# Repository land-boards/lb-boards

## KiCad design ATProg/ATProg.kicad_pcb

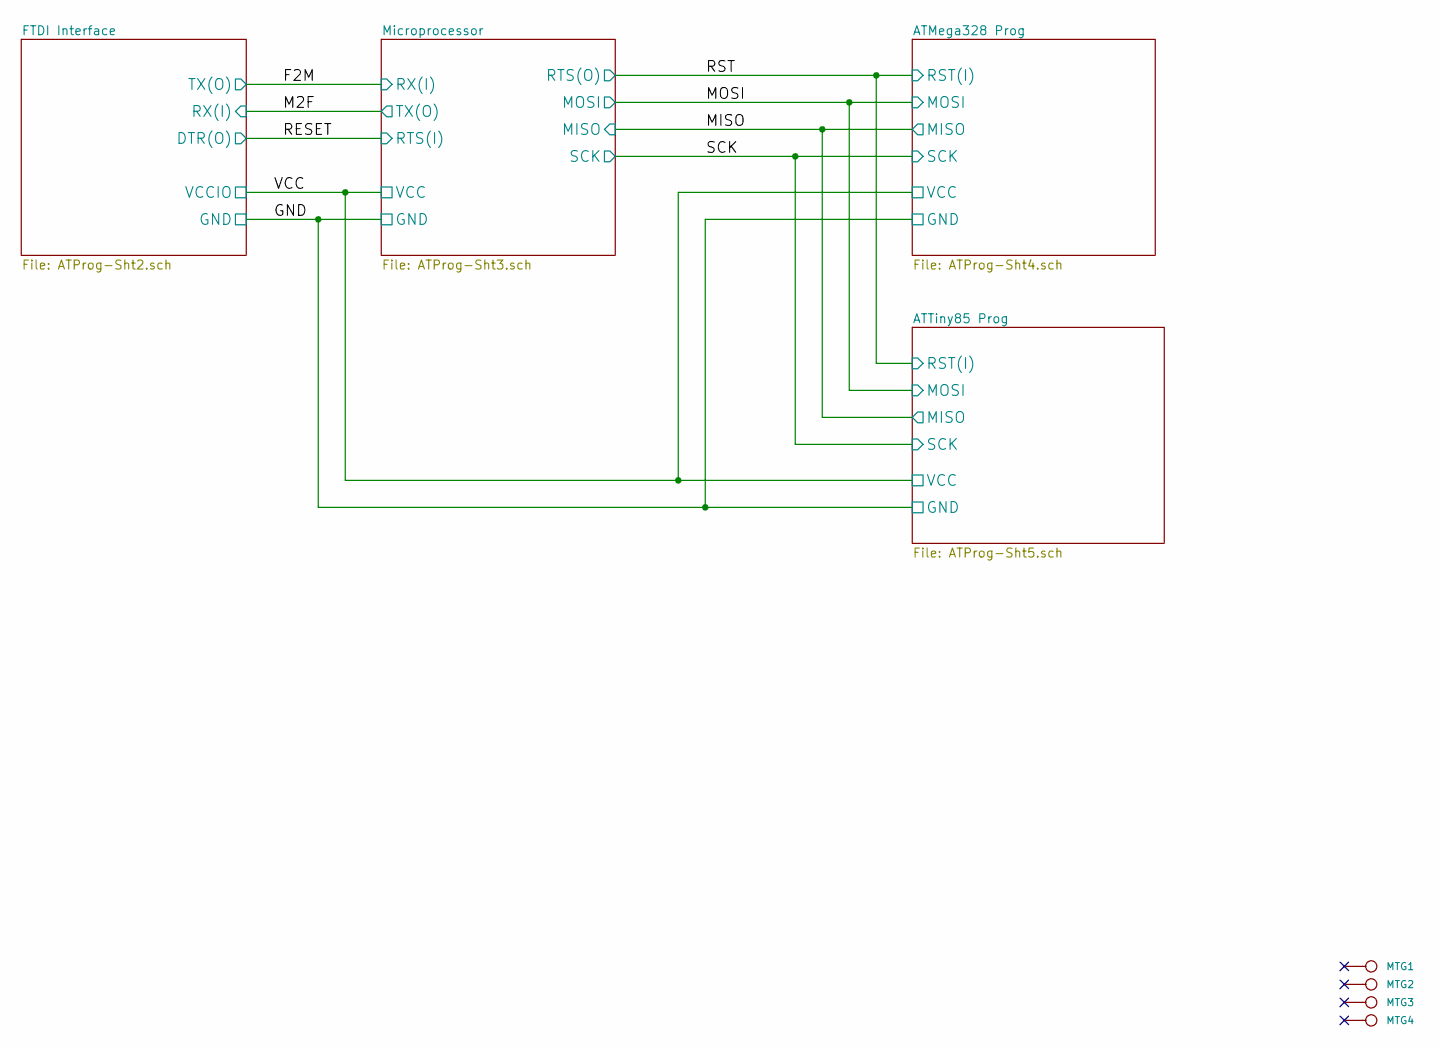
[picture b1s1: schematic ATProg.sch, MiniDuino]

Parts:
MTG1, MTG2, MTG3, MTG4: CONN_1; MTG-4-40

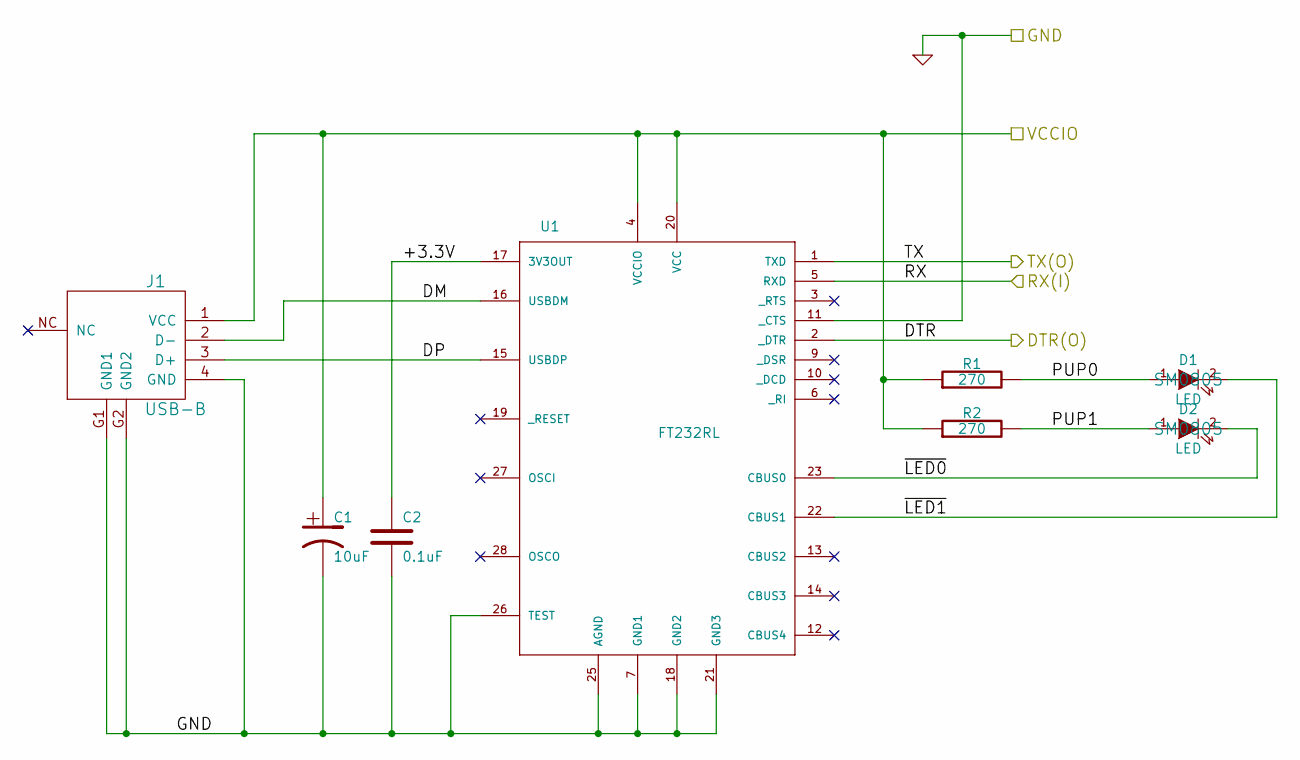
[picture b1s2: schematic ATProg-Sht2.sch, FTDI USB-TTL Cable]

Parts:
C1: 10uF; SM1210; MfgPN CC121ZKY5V8BB106
C2: 0.1uF; SM0805; MfgPN GRM155F51E104ZA1J
D1, D2: LED; SM0805
J1: USB-B; USB-B-MINI; MfgPN UX60SC-MB-5ST(80)
R1: 270; SM0805; MfgPN CRG0805F270R
R2: 270; SM0805
U1: FT232RL; SSOP28; MfgPN FT232RL-REEL

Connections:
+5V: C1.1, J1.1 (VCC), R1.1, R2.1, U1.4 (VCCIO), U1.20 (VCC); also elsewhere on the board
/FTDI Interface/+3.3V: C2.1, U1.17 (3V3OUT)
/FTDI Interface/DM: J1.2 (D-), U1.16 (USBDM)
/FTDI Interface/DP: J1.3 (D+), U1.15 (USBDP)
/FTDI Interface/DTR(O): U1.2 (_DTR); also elsewhere on the board
/FTDI Interface/PUP0: D1.1 (A), R1.2
/FTDI Interface/PUP1: D2.1 (A), R2.2
/FTDI Interface/RXFTDI: U1.5 (RXD); also elsewhere on the board
/FTDI Interface/~LED0: D2.2 (K), U1.23 (CBUS0)
/FTDI Interface/~LED1: D1.2 (K), U1.22 (CBUS1)
/Microprocessor/RXCPU: U1.1 (TXD); also elsewhere on the board
GND: C1.2, C2.2, J1.4 (GND), J1.G1 (GND1), J1.G2 (GND2), U1.7 (GND1), U1.11 (_CTS), U1.18 (GND2), U1.21 (GND3), U1.25 (AGND), U1.26 (TEST); also elsewhere on the board

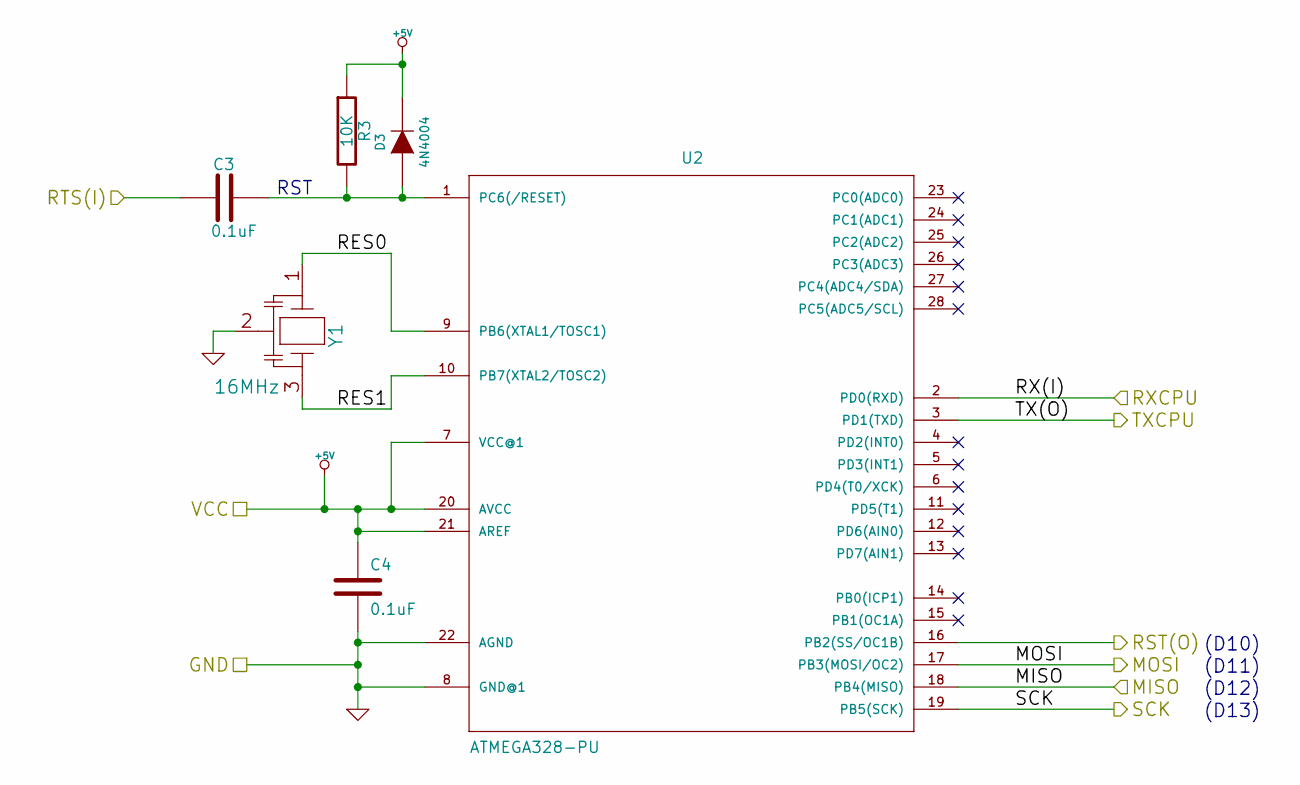
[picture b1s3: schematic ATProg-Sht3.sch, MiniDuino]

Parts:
C3, C4: 0.1uF; SM0805
D3: 4N4004; D3
R3: 10K; SM0805
U2: ATMEGA328-PU; DIP-28__300
Y1: 16MHz; SIL-3

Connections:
+5V: C4.1, D3.2 (K), R3.1, U2.7 (VCC@1), U2.20 (AVCC), U2.21 (AREF); also elsewhere on the board
/ATMega328 Prog/MISO: U2.18 (PB4(MISO)); also elsewhere on the board
/ATMega328 Prog/MOSI: U2.17 (PB3(MOSI/OC2)); also elsewhere on the board
/ATMega328 Prog/SCK: U2.19 (PB5(SCK)); also elsewhere on the board
/FTDI Interface/DTR(O): C3.1; also elsewhere on the board
/FTDI Interface/RXFTDI: U2.3 (PD1(TXD)); also elsewhere on the board
/ISP Connector/RST: U2.16 (PB2(SS/OC1B)); also elsewhere on the board
/Microprocessor/RES0: U2.9 (PB6(XTAL1/TOSC1)), Y1.1
/Microprocessor/RES1: U2.10 (PB7(XTAL2/TOSC2)), Y1.3
/Microprocessor/RXCPU: U2.2 (PD0(RXD)); also elsewhere on the board
GND: C4.2, U2.8 (GND@1), U2.22 (AGND), Y1.2; also elsewhere on the board
unnamed: C3.2, D3.1 (A), R3.2, U2.1 (PC6(/RESET))

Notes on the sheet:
(D13)
(D12)
(D11)
RST
(D10)

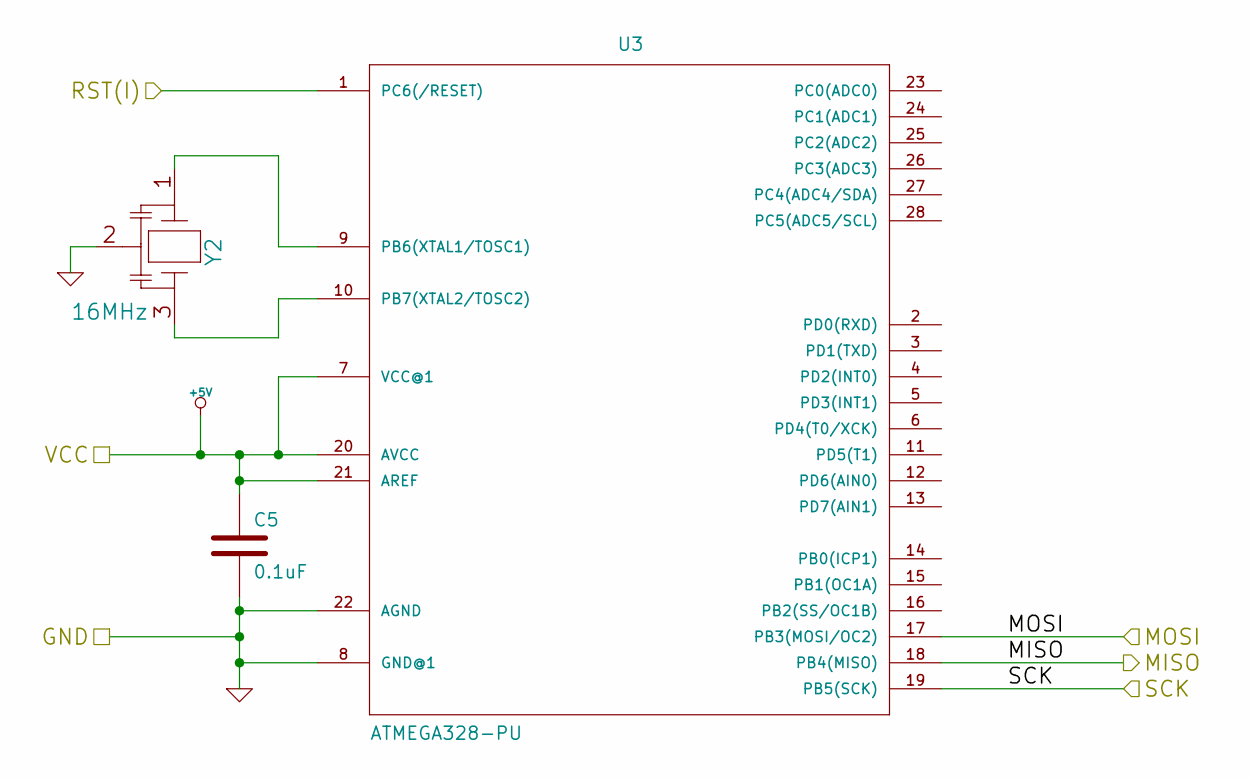
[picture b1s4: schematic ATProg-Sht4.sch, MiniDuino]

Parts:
C5: 0.1uF; SM0805
U3: ATMEGA328-PU; DIP-28__300
Y2: 16MHz; SIL-3

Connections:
+5V: C5.1, U3.7 (VCC@1), U3.20 (AVCC), U3.21 (AREF); also elsewhere on the board
/ATMega328 Prog/MISO: U3.18 (PB4(MISO)); also elsewhere on the board
/ATMega328 Prog/MOSI: U3.17 (PB3(MOSI/OC2)); also elsewhere on the board
/ATMega328 Prog/SCK: U3.19 (PB5(SCK)); also elsewhere on the board
/ISP Connector/RST: U3.1 (PC6(/RESET)); also elsewhere on the board
GND: C5.2, U3.8 (GND@1), U3.22 (AGND), Y2.2; also elsewhere on the board
unnamed: U3.9 (PB6(XTAL1/TOSC1)), Y2.1
unnamed: U3.10 (PB7(XTAL2/TOSC2)), Y2.3

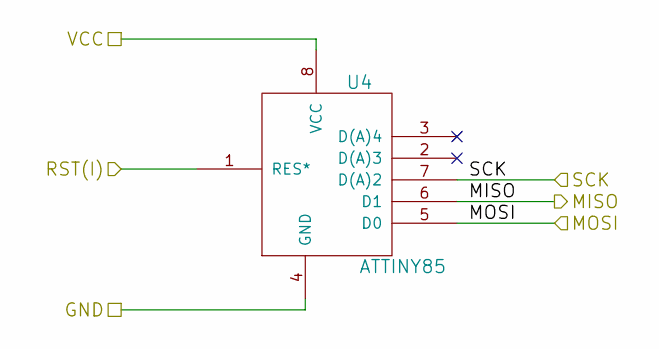
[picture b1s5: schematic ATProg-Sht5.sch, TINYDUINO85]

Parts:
U4: ATTINY85; DIP-8__300

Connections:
+5V: U4.8 (VCC); also elsewhere on the board
/ATMega328 Prog/MISO: U4.6 (D1); also elsewhere on the board
/ATMega328 Prog/MOSI: U4.5 (D0); also elsewhere on the board
/ATMega328 Prog/SCK: U4.7 (D(A)2); also elsewhere on the board
/ISP Connector/RST: U4.1 (RES*); also elsewhere on the board
GND: U4.4 (GND); also elsewhere on the board

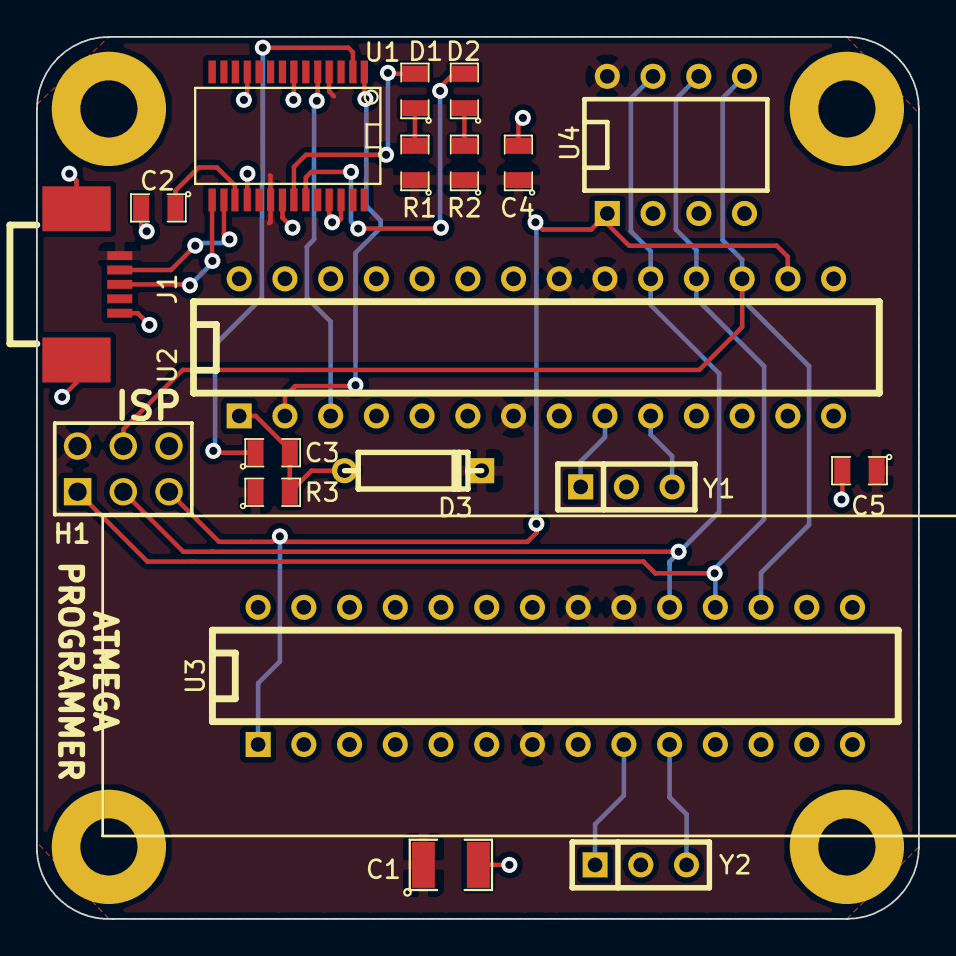
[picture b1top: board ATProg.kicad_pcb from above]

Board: 2 copper layers, 49.0 x 49.0 mm, 23 parts (0 on the bottom side), 21 nets.

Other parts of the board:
H1: CONN_3X2; pin_array_3x2

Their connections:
+5V: H1.2; also elsewhere on the board
/ATMega328 Prog/MISO: H1.1; also elsewhere on the board
/ATMega328 Prog/MOSI: H1.4; also elsewhere on the board
/ATMega328 Prog/SCK: H1.3; also elsewhere on the board
/ISP Connector/RST: H1.5; also elsewhere on the board
GND: H1.6; also elsewhere on the board

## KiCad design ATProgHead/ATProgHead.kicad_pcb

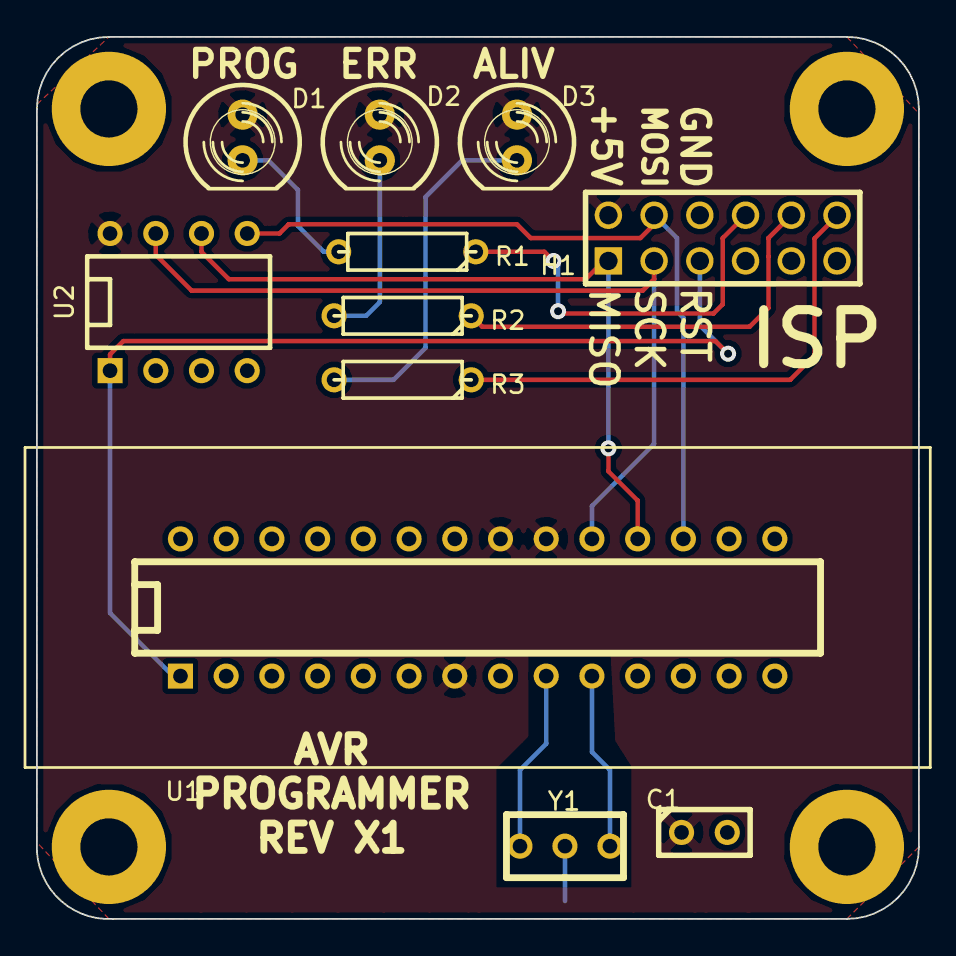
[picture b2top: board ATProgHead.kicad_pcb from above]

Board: 2 copper layers, 49.0 x 49.0 mm, 15 parts (0 on the bottom side), 14 nets.

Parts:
C1: 0.1uF; C1
D1, D2, D3: LED; LED-5MM
H1: CONN_6X2; pin_array_6x2
MTG1, MTG2, MTG3, MTG4: CONN_1; MTG-4-40
R1, R2, R3: 330; R3
U1: ATMEGA328-PU; TEXTOOL-28N
U2: ATTINY85; DIP-8__300
Y1: 16MHz; RESON_3PIN

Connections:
+5V: C1.1, D1.1, D2.1, D3.1, H1.2, U1.7, U1.20, U1.21, U2.8
/ER: D2.2, R2.2
/ERR: H1.10, R2.1
/HB: D3.2, R3.2
/HTBT: H1.12, R3.1
/MISO: H1.1, U1.18, U2.6
/MOSI: H1.4, U1.17, U2.5
/PG: D1.2, R1.2
/PROG: H1.8, R1.1
/RST: H1.5, U1.1, U2.1
/SCK: H1.3, U1.19, U2.7
GND: C1.2, H1.6, U1.8, U1.22, U2.4, Y1.2
unnamed: U1.10, Y1.3
unnamed: U1.9, Y1.1

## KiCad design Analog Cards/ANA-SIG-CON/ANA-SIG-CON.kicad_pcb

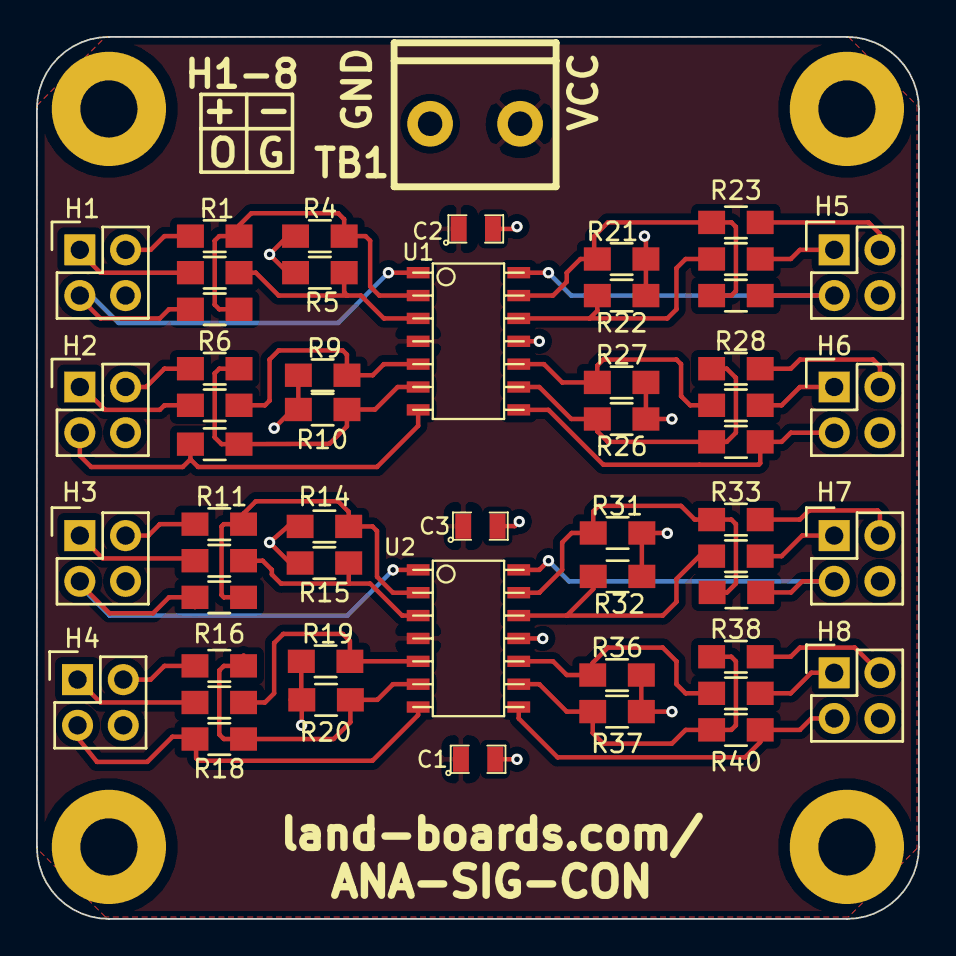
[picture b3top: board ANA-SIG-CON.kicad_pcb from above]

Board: 2 copper layers, 49.0 x 49.0 mm, 58 parts (0 on the bottom side), 42 nets.

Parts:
C1, C2, C3: C; SM0805
H1, H2, H3, H4, H5, H6, H7, H8: CONN_01X04; Pin_Header_Straight_2x02
MTG1, MTG2, MTG3, MTG4: CONN_1; MTG-4-40
R1, R2, R4, R5, R6, R7, R9, R10, R11, R12, R14, R15, R16, R17, R19, R20, R21, R22, R23, R24, R26, R27, R28, R29, R31, R32, R33, R34, R36, R37, R38, R39: 1K; R_0805_HandSoldering
R3, R8, R13, R18, R25, R30, R35, R40: 1M; R_0805_HandSoldering
TB1: CONN_2; TB2-5MM
U1, U2: LM324N; so-14

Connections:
/I1+: H1.1, R2.1
/I1-: H1.2, R1.1
/I2+: H2.1, R7.1
/I2-: H2.2, R6.1
/I3+: H3.1, R12.1
/I3-: H3.2, R11.1
/I4+: H4.1, R17.1
/I4-: H4.2, R16.1
/I5+: H5.1, R24.1
/I5-: H5.2, R23.1
/I6+: H6.1, R29.1
/I6-: H6.2, R28.1
/I7+: H7.1, R34.1
/I7-: H7.2, R33.1
/I8+: H8.1, R39.1
/I8-: H8.2, R38.1
/O1: H1.3, R3.2, U1.1
/O2: H2.3, R8.2, U1.7
/O3: H3.3, R13.2, U2.1
/O4: H4.3, R18.2, U2.7
/O5: H5.3, R25.2, U1.14
/O6: H6.3, R30.2, U1.8
/O7: H7.3, R35.2, U2.14
/O8: H8.3, R40.2, U2.8
GND: C1.2, C2.2, C3.2, H1.4, H2.4, H3.4, H4.4, H5.4, H6.4, H7.4, H8.4, R4.1, R5.1, R9.1, R10.1, R14.1, R15.1, R19.1, R20.1, R21.1, R22.1, R26.1, R27.1, R31.1, R32.1, R36.1, R37.1, TB1.1, U1.11, U2.11
unnamed: R1.2, R3.1, R4.2, U1.2
unnamed: R2.2, R5.2, U1.3
unnamed: R7.2, R9.2, U1.5
unnamed: R6.2, R8.1, R10.2, U1.6
unnamed: R11.2, R13.1, R14.2, U2.2
unnamed: R12.2, R15.2, U2.3
unnamed: R16.2, R18.1, R20.2, U2.6
unnamed: R17.2, R19.2, U2.5
unnamed: R21.2, R23.2, R25.1, U1.13
unnamed: R22.2, R24.2, U1.12
unnamed: R26.2, R28.2, R30.1, U1.9
unnamed: R27.2, R29.2, U1.10
unnamed: R31.2, R33.2, R35.1, U2.13
unnamed: R32.2, R34.2, U2.12
unnamed: R36.2, R39.2, U2.10
unnamed: R37.2, R38.2, R40.1, U2.9
VAA: C1.1, C2.1, C3.1, TB1.2, U1.4, U2.4

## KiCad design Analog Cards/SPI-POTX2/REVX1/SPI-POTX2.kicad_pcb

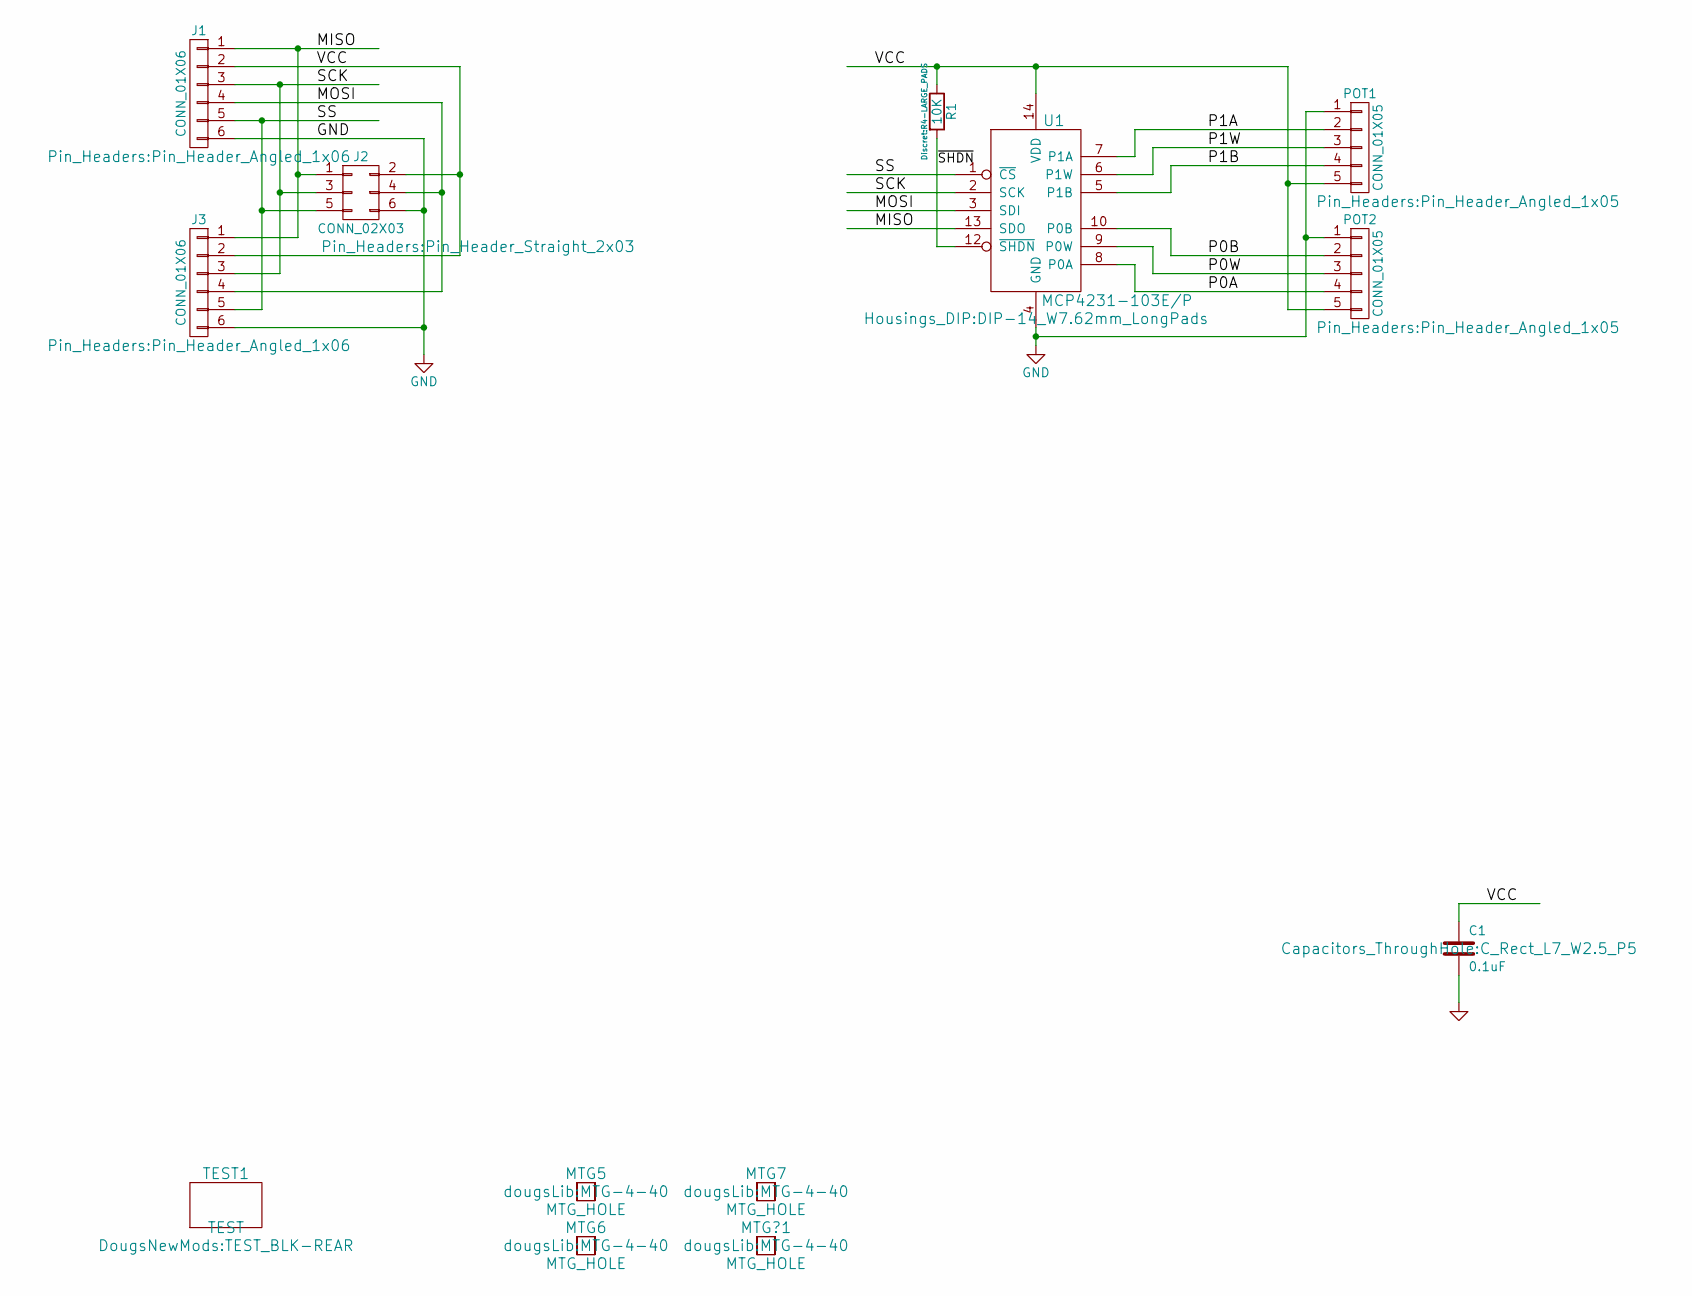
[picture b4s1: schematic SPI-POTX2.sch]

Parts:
C1: 0.1uF; C_Rect_L7_W2.5_P5
J1, J3: CONN_01X06; Pin_Header_Angled_1x06
J2: CONN_02X03; Pin_Header_Straight_2x03
MTG5, MTG6, MTG7: MTG_HOLE; MTG-4-40
MTG?1: MTG_HOLE; MTG-4-40
POT1, POT2: CONN_01X05; Pin_Header_Angled_1x05
R1: 10K; R4-LARGE_PADS
TEST1: TEST; TEST_BLK-REAR
U1: MCP4231-103E/P; DIP-14_W7.62mm_LongPads

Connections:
/MISO: J1.1, J2.1, J3.1, U1.13 (SDO)
/MOSI: J1.4, J2.4, J3.4, U1.3 (SDI)
/P0A: POT2.4, U1.8 (P0A)
/P0B: POT2.2, U1.10 (P0B)
/P0W: POT2.3, U1.9 (P0W)
/P1A: POT1.4, U1.5 (P1B)
/P1B: POT1.2, U1.7 (P1A)
/P1W: POT1.3, U1.6 (P1W)
/SCK: J1.3, J2.3, J3.3, U1.2 (SCK)
/SS: J1.5, J2.5, J3.5, U1.1 (~CS)
/VCC: C1.1, J1.2, J2.2, J3.2, POT1.5, POT2.5, R1.1, U1.14 (VDD)
/~SHDN: R1.2, U1.12 (~SHDN)
GND: C1.2, J1.6, J2.6, J3.6, POT1.1, POT2.1, U1.4 (GND)

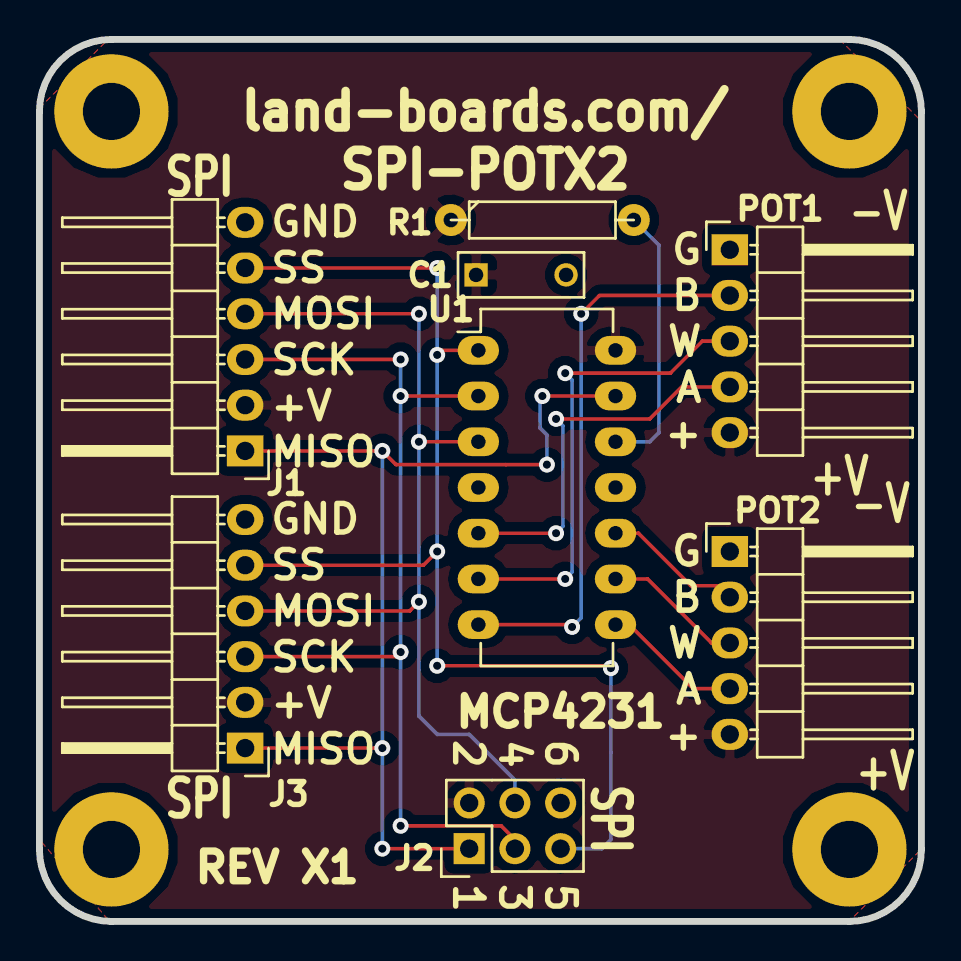
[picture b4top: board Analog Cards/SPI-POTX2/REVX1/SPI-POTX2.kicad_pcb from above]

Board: 2 copper layers, 49.0 x 49.0 mm, 13 parts (0 on the bottom side), 13 nets.

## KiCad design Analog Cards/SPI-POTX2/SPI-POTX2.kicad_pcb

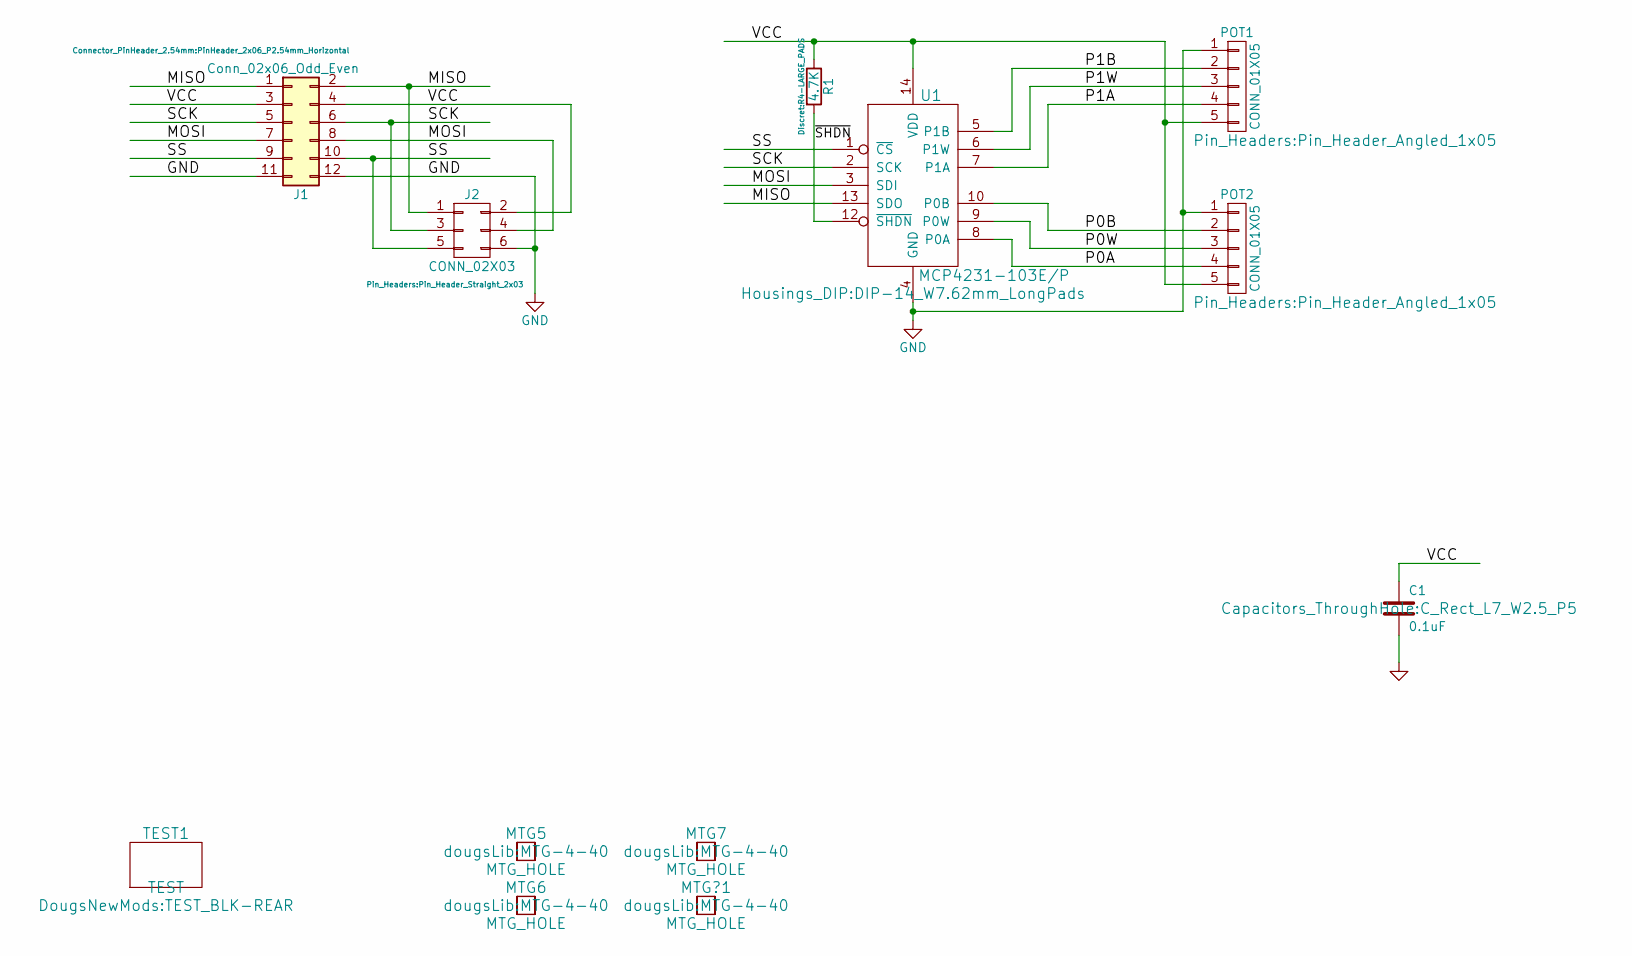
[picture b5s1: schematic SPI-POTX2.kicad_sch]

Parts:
C1: 0.1uF; C_Rect_L7_W2.5_P5
J1: Conn_02x06_Odd_Even; PinHeader_2x06_P2.54mm_Horizontal
J2: CONN_02X03; Pin_Header_Straight_2x03
MTG5, MTG6, MTG7: MTG_HOLE; MTG-4-40
MTG?1: MTG_HOLE; MTG-4-40
POT1, POT2: CONN_01X05; Pin_Header_Angled_1x05
R1: 4.7K; R4-LARGE_PADS
TEST1: TEST; TEST_BLK-REAR
U1: MCP4231-103E/P; DIP-14_W7.62mm_LongPads

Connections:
/MISO: J1.1, J1.2, J2.1, U1.13 (SDO)
/MOSI: J1.7, J1.8, J2.4, U1.3 (SDI)
/P0A: POT2.4, U1.8 (P0A)
/P0B: POT2.2, U1.10 (P0B)
/P0W: POT2.3, U1.9 (P0W)
/P1A: POT1.4, U1.7 (P1A)
/P1B: POT1.2, U1.5 (P1B)
/P1W: POT1.3, U1.6 (P1W)
/SCK: J1.5, J1.6, J2.3, U1.2 (SCK)
/SS: J1.9, J1.10, J2.5, U1.1 (~CS)
/VCC: C1.1, J1.3, J1.4, J2.2, POT1.5, POT2.5, R1.1, U1.14 (VDD)
/~SHDN: R1.2, U1.12 (~SHDN)
GND: C1.2, J1.11, J1.12, J2.6, POT1.1, POT2.1, U1.4 (GND)

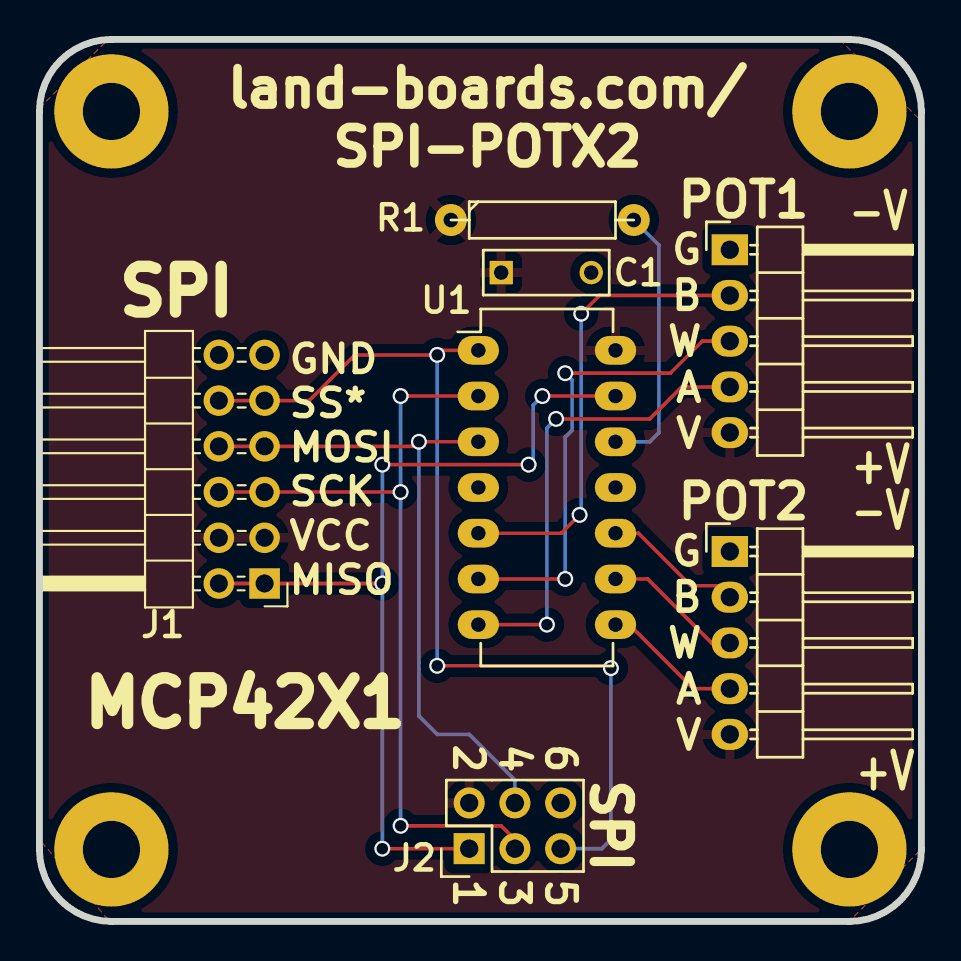
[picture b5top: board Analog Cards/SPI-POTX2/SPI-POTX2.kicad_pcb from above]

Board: 2 copper layers, 49.0 x 49.0 mm, 12 parts (0 on the bottom side), 13 nets.

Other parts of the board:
TEST: TEST; TEST_BLK-REAR

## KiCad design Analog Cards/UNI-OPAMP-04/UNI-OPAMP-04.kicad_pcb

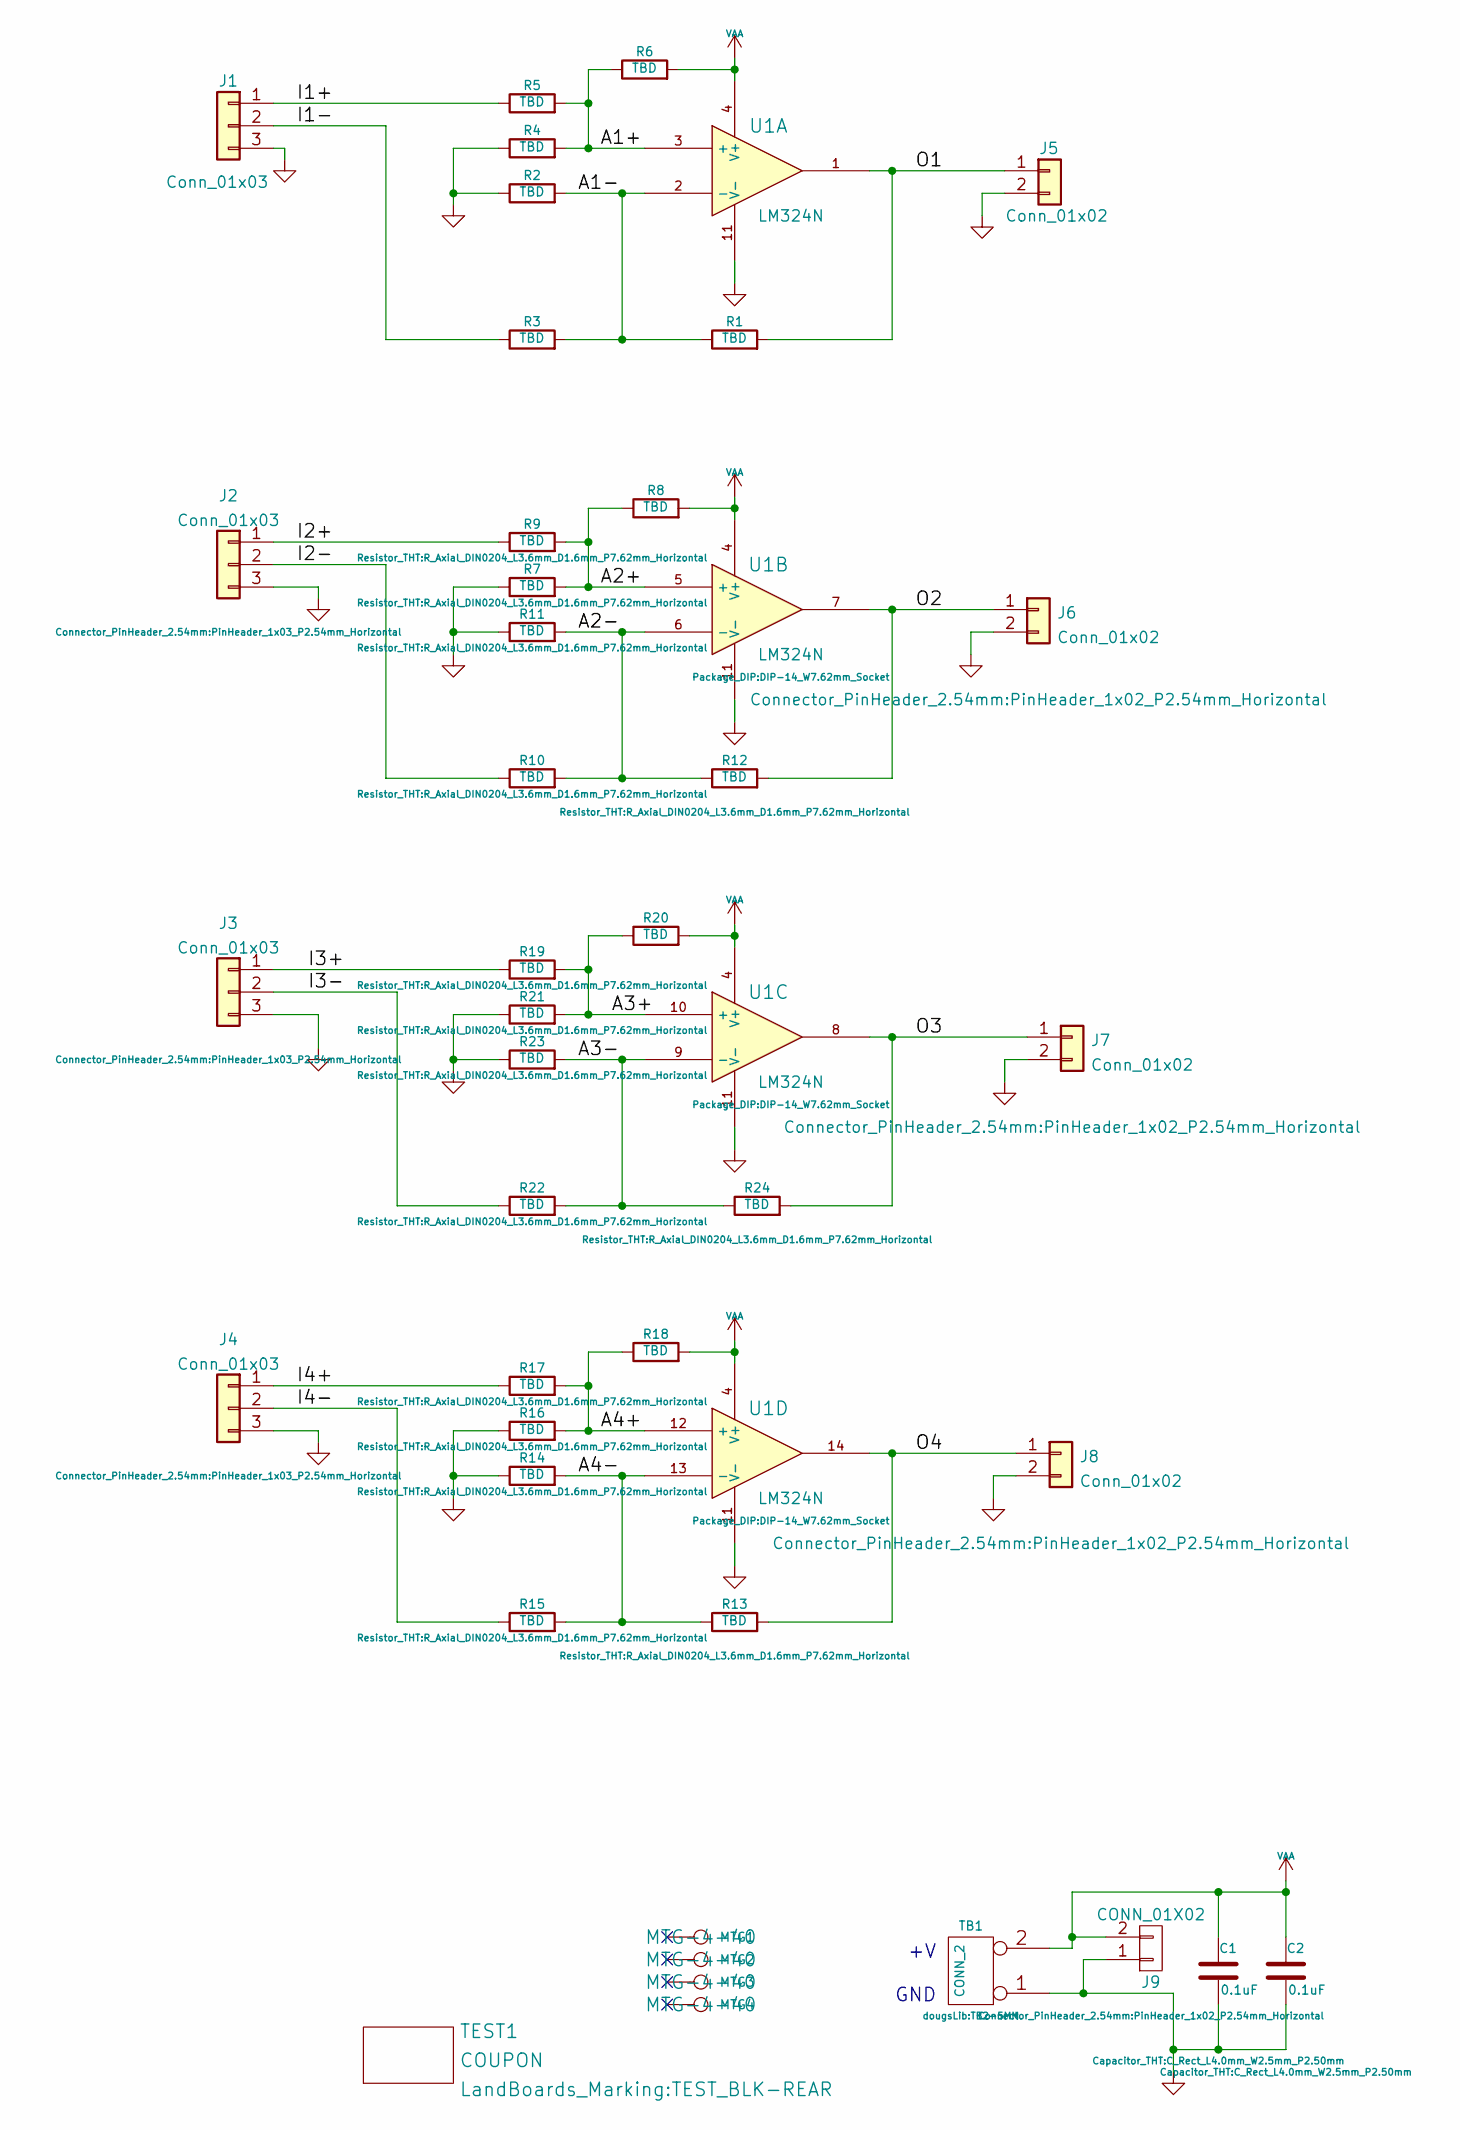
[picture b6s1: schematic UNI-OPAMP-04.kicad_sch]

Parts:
C1, C2: 0.1uF; C_Rect_L4.0mm_W2.5mm_P2.50mm
J1, J2, J3, J4: Conn_01x03; PinHeader_1x03_P2.54mm_Horizontal
J5, J6, J7, J8: Conn_01x02; PinHeader_1x02_P2.54mm_Horizontal
J9: CONN_01X02; PinHeader_1x02_P2.54mm_Horizontal
MTG1, MTG2, MTG3, MTG4: CONN_1; MTG-4-40
R1, R2, R3, R4, R5, R6, R7, R8, R9, R10, R11, R12, R13, R14, R15, R16, R17, R18, R19, R20, R21, R22, R23, R24: TBD; R_Axial_DIN0204_L3.6mm_D1.6mm_P7.62mm_Horizontal
TB1: CONN_2; TB2-5MM
TEST1: COUPON; TEST_BLK-REAR
U1: LM324N; DIP-14_W7.62mm_Socket

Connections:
/A1+: R4.2, R5.2, R6.1, U1.3 (+)
/A1-: R1.1, R2.2, R3.2, U1.2 (-)
/A2+: R7.2, R8.1, R9.2, U1.5 (+)
/A2-: R10.2, R11.2, R12.1, U1.6 (-)
/A3+: R19.2, R20.1, R21.2, U1.10 (+)
/A3-: R22.2, R23.2, R24.1, U1.9 (-)
/A4+: R16.2, R17.2, R18.1, U1.12 (+)
/A4-: R13.1, R14.2, R15.2, U1.13 (-)
/I1+: J1.1, R5.1
/I1-: J1.2, R3.1
/I2+: J2.1, R9.1
/I2-: J2.2, R10.1
/I3+: J3.1, R19.1
/I3-: J3.2, R22.1
/I4+: J4.1, R17.1
/I4-: J4.2, R15.1
/O1: J5.1, R1.2, U1.1
/O2: J6.1, R12.2, U1.7
/O3: J7.1, R24.2, U1.8
/O4: J8.1, R13.2, U1.14
GND: C1.2, C2.2, J1.3, J2.3, J3.3, J4.3, J5.2, J6.2, J7.2, J8.2, J9.1, R2.1, R4.1, R7.1, R11.1, R14.1, R16.1, R21.1, R23.1, TB1.1, U1.11 (V-)
VAA: C1.1, C2.1, J9.2, R6.2, R8.2, R18.2, R20.2, TB1.2 (PM), U1.4 (V+)

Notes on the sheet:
+V GND
